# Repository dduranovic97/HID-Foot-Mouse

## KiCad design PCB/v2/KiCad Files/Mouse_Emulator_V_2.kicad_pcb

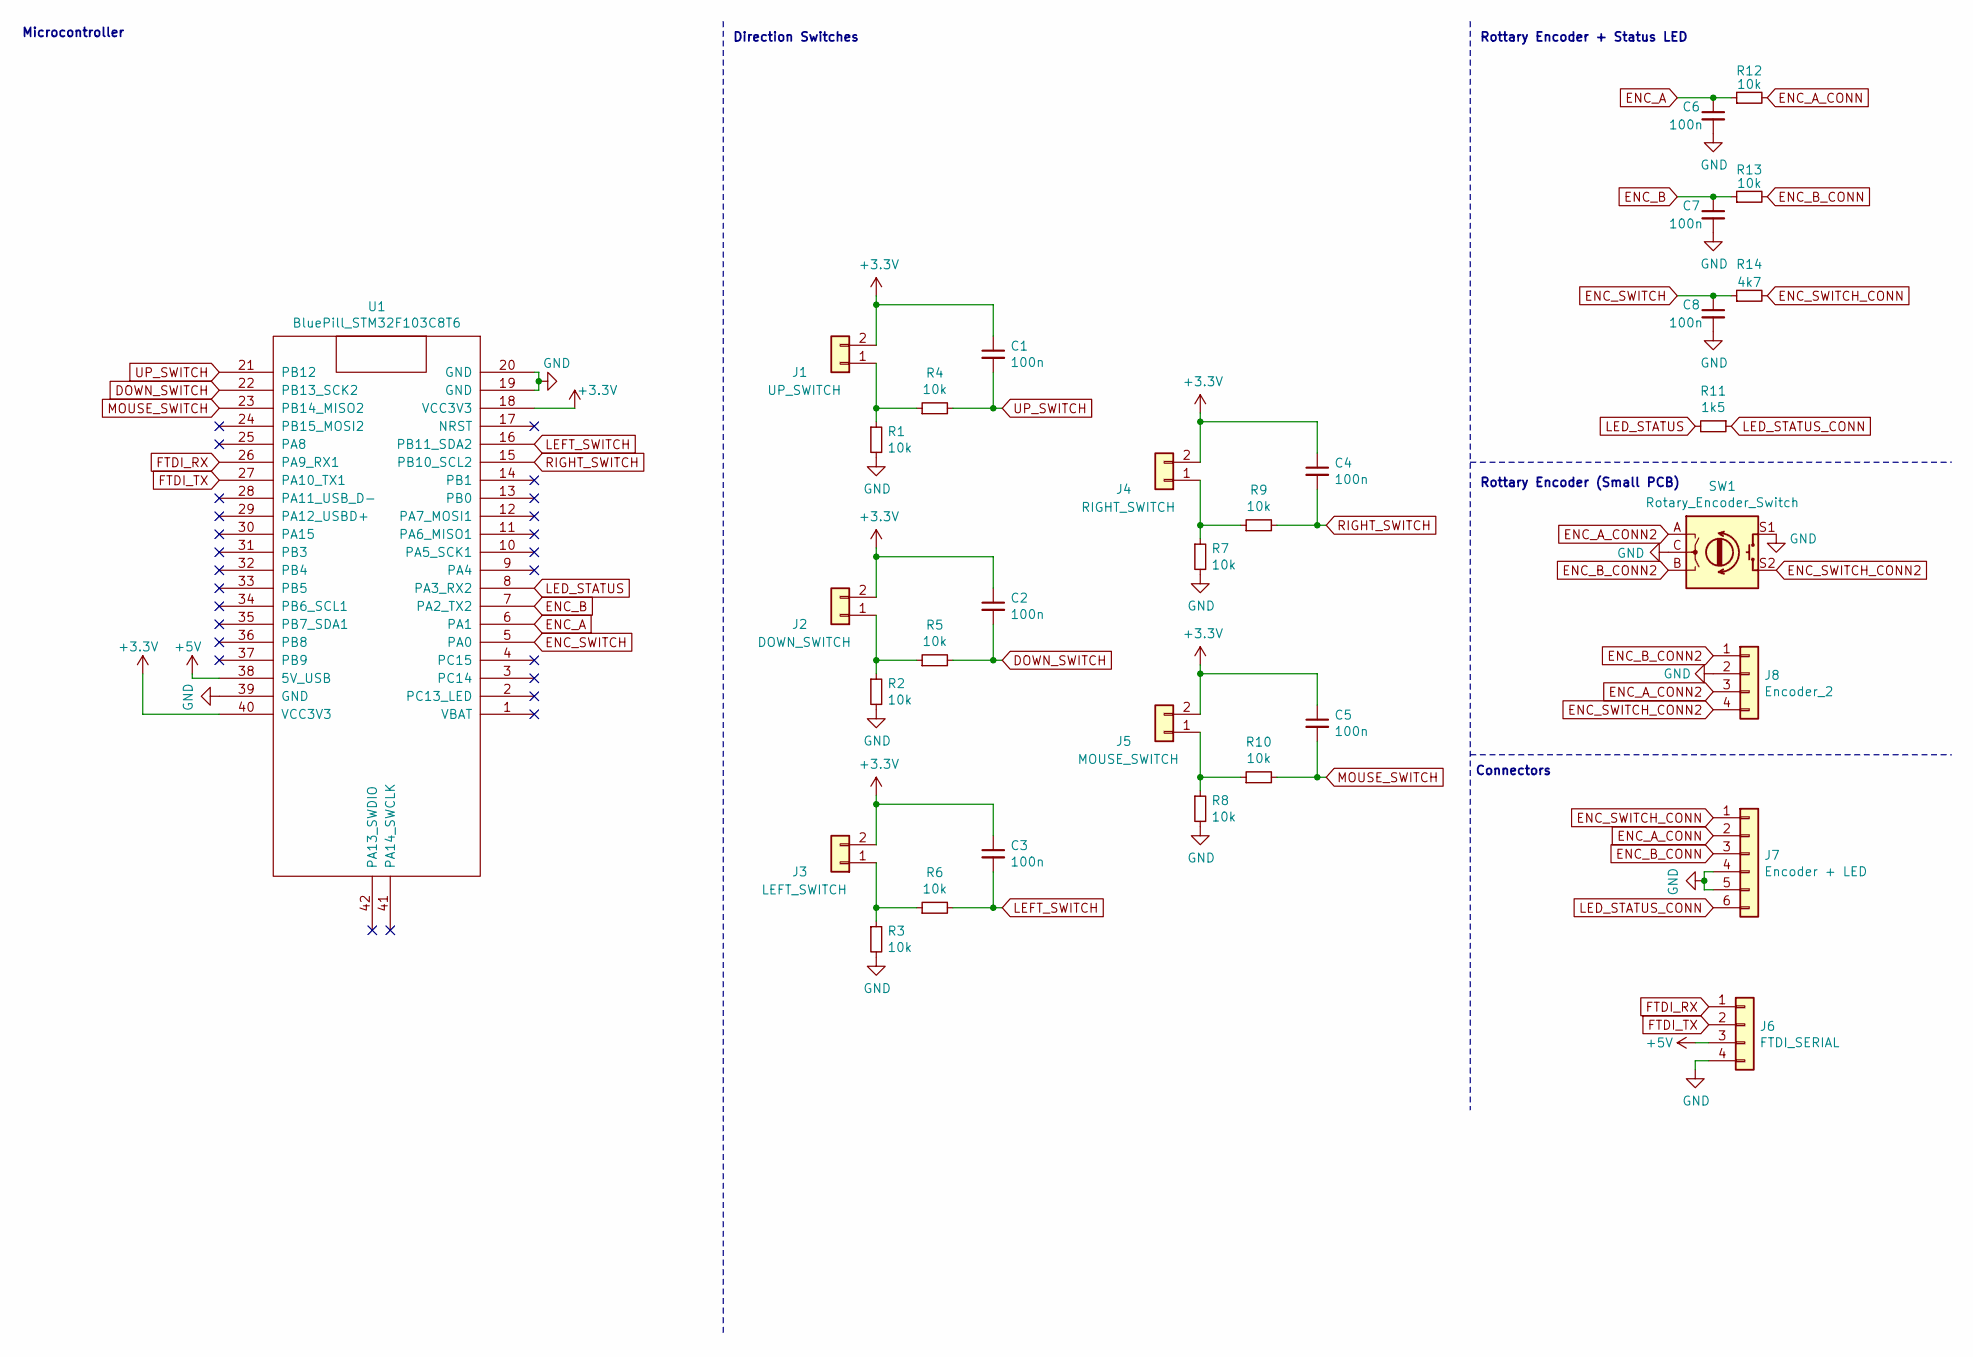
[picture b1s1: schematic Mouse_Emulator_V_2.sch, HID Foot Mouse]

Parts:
C1, C2, C3, C4, C5, C6, C7, C8: 100n; C_Rect_L7.2mm_W2.5mm_P5.00mm_FKS2_FKP2_MKS2_MKP2
J1: UP_SWITCH; JST_EH_B2B-EH-A_1x02_P2.50mm_Vertical
J2: DOWN_SWITCH; JST_EH_B2B-EH-A_1x02_P2.50mm_Vertical
J3: LEFT_SWITCH; JST_EH_B2B-EH-A_1x02_P2.50mm_Vertical
J4: RIGHT_SWITCH; JST_EH_B2B-EH-A_1x02_P2.50mm_Vertical
J5: MOUSE_SWITCH; JST_EH_B2B-EH-A_1x02_P2.50mm_Vertical
J6: FTDI_SERIAL; JST_EH_B4B-EH-A_1x04_P2.50mm_Vertical
J7: Encoder + LED; JST_EH_B6B-EH-A_1x06_P2.50mm_Vertical
J8: Encoder_2; JST_EH_B4B-EH-A_1x04_P2.50mm_Vertical
R1, R2, R3, R4, R5, R6, R7, R8, R9, R10, R12, R13: 10k; R_Axial_DIN0207_L6.3mm_D2.5mm_P10.16mm_Horizontal
R11: 1k5; R_Axial_DIN0207_L6.3mm_D2.5mm_P10.16mm_Horizontal
R14: 4k7; R_Axial_DIN0207_L6.3mm_D2.5mm_P10.16mm_Horizontal
SW1: Rotary_Encoder_Switch; RotaryEncoder_Alps_EC11E-Switch_Vertical_H20mm
U1: BluePill_STM32F103C8T6; BluePill_STM32F103C

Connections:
+3V3: C1.1, C2.1, C3.1, C4.1, C5.1, J1.2, J2.2, J3.2, J4.2, J5.2, U1.18 (VCC3V3), U1.40 (VCC3V3)
+5V: J6.3, U1.38 (5V_USB)
DOWN_SWITCH: C2.2, R5.2, U1.22 (PB13_SCK2)
ENC_A: C6.1, R12.1, U1.6 (PA1)
ENC_A_CONN: J7.2, R12.2
ENC_A_CONN2: J8.3, SW1.A; also elsewhere on the board
ENC_B: C7.1, R13.1, U1.7 (PA2_TX2)
ENC_B_CONN: J7.3, R13.2
ENC_B_CONN2: J8.1, SW1.B; also elsewhere on the board
ENC_SWITCH: C8.1, R14.1, U1.5 (PA0)
ENC_SWITCH_CONN: J7.1, R14.2
ENC_SWITCH_CONN2: J8.4, SW1.S2; also elsewhere on the board
FTDI_RX: J6.1, U1.26 (PA9_RX1)
FTDI_TX: J6.2, U1.27 (PA10_TX1)
GND: C6.2, C7.2, C8.2, J6.4, J7.4, J7.5, J8.2, R1.2, R2.2, R3.2, R7.2, R8.2, SW1.C, SW1.S1, U1.19 (GND), U1.20 (GND), U1.39 (GND); also elsewhere on the board
LED_STATUS: R11.2, U1.8 (PA3_RX2)
LED_STATUS_CONN: J7.6, R11.1
LEFT_SWITCH: C3.2, R6.2, U1.16 (PB11_SDA2)
MOUSE_SWITCH: C5.2, R10.2, U1.23 (PB14_MISO2)
unnamed: J1.1, R1.1, R4.1
unnamed: J2.1, R2.1, R5.1
unnamed: J3.1, R3.1, R6.1
unnamed: J4.1, R7.1, R9.1
unnamed: J5.1, R8.1, R10.1
RIGHT_SWITCH: C4.2, R9.2, U1.15 (PB10_SCL2)
UP_SWITCH: C1.2, R4.2, U1.21 (PB12)

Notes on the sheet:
Microcontroller
Direction Switches
Rottary Encoder + Status LED
Connectors
Rottary Encoder (Small PCB)

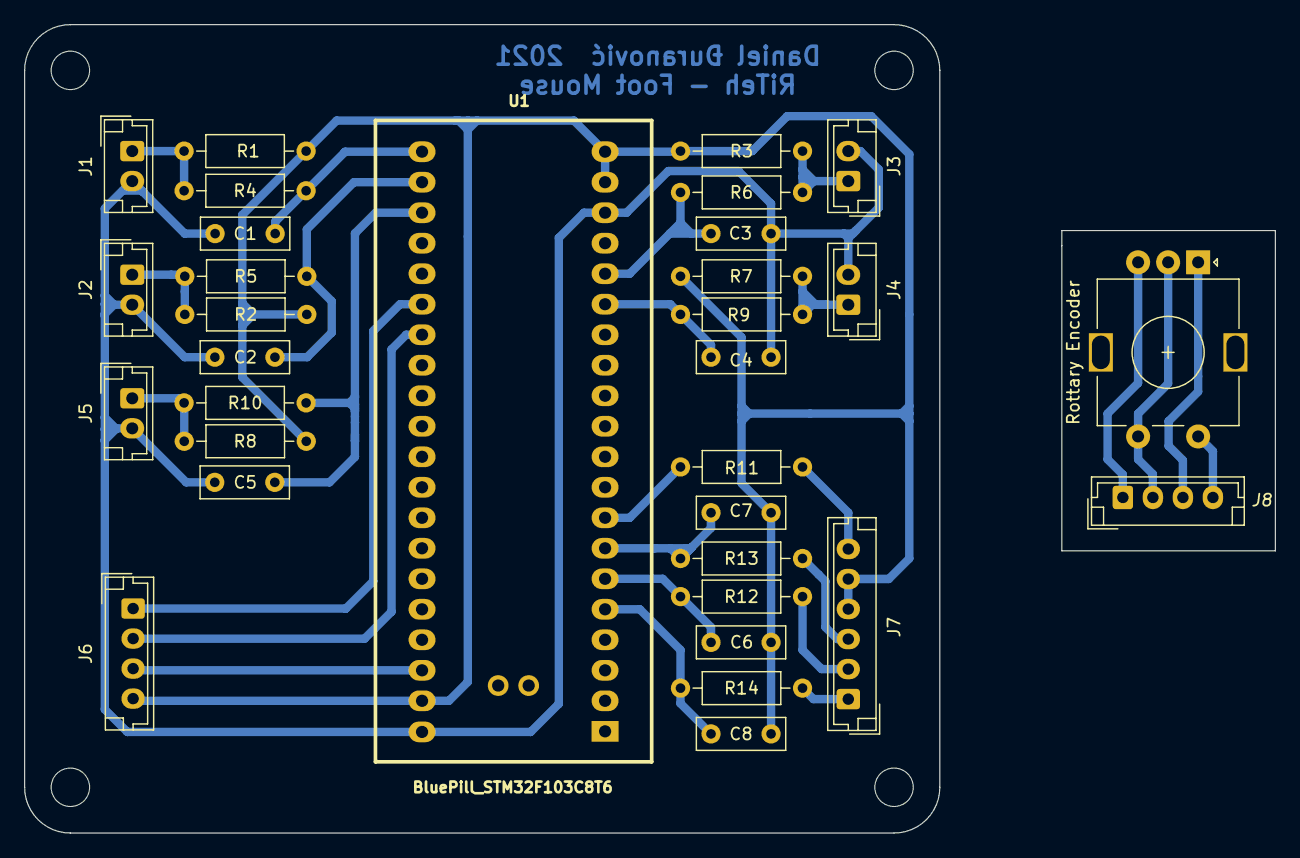
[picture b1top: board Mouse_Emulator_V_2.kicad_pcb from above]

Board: 2 copper layers, 104.1 x 67.3 mm, 32 parts (0 on the bottom side), 26 nets.

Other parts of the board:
Rottary Encoder: Rotary_Encoder_Switch; RotaryEncoder_Alps_EC11E-Switch_Vertical_H20mm

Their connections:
ENC_A_CONN2: Rottary Encoder.A; also elsewhere on the board
ENC_B_CONN2: Rottary Encoder.B; also elsewhere on the board
ENC_SWITCH_CONN2: Rottary Encoder.S2; also elsewhere on the board
GND: Rottary Encoder.C, Rottary Encoder.S1; also elsewhere on the board

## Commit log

2021-08-25 First Commit
    Problem kod softwarea - Windows ga odjednom ne prepoznaje kao HID uređaj ("Device Mulfunctioned in past")
2021-09-02 Fixed encoder
2021-09-03 Fixed counter and trigering interupt
    Fixed counter incrementing to max value, corected counter values, added map() function to mouseRange, the interupt doesn't trigger anymore when board is plugged in USB Port
2021-09-03 Polished some things
2021-09-03 Schematic
2021-09-03 Schematic V2
2021-09-03 Pins definition + Schematic
2021-09-05 Big Commit
    Pins definition, schematic, PCB layout, Box Dimensions, pictures and so on.
2021-09-19 Commit 2
    Parameters change
